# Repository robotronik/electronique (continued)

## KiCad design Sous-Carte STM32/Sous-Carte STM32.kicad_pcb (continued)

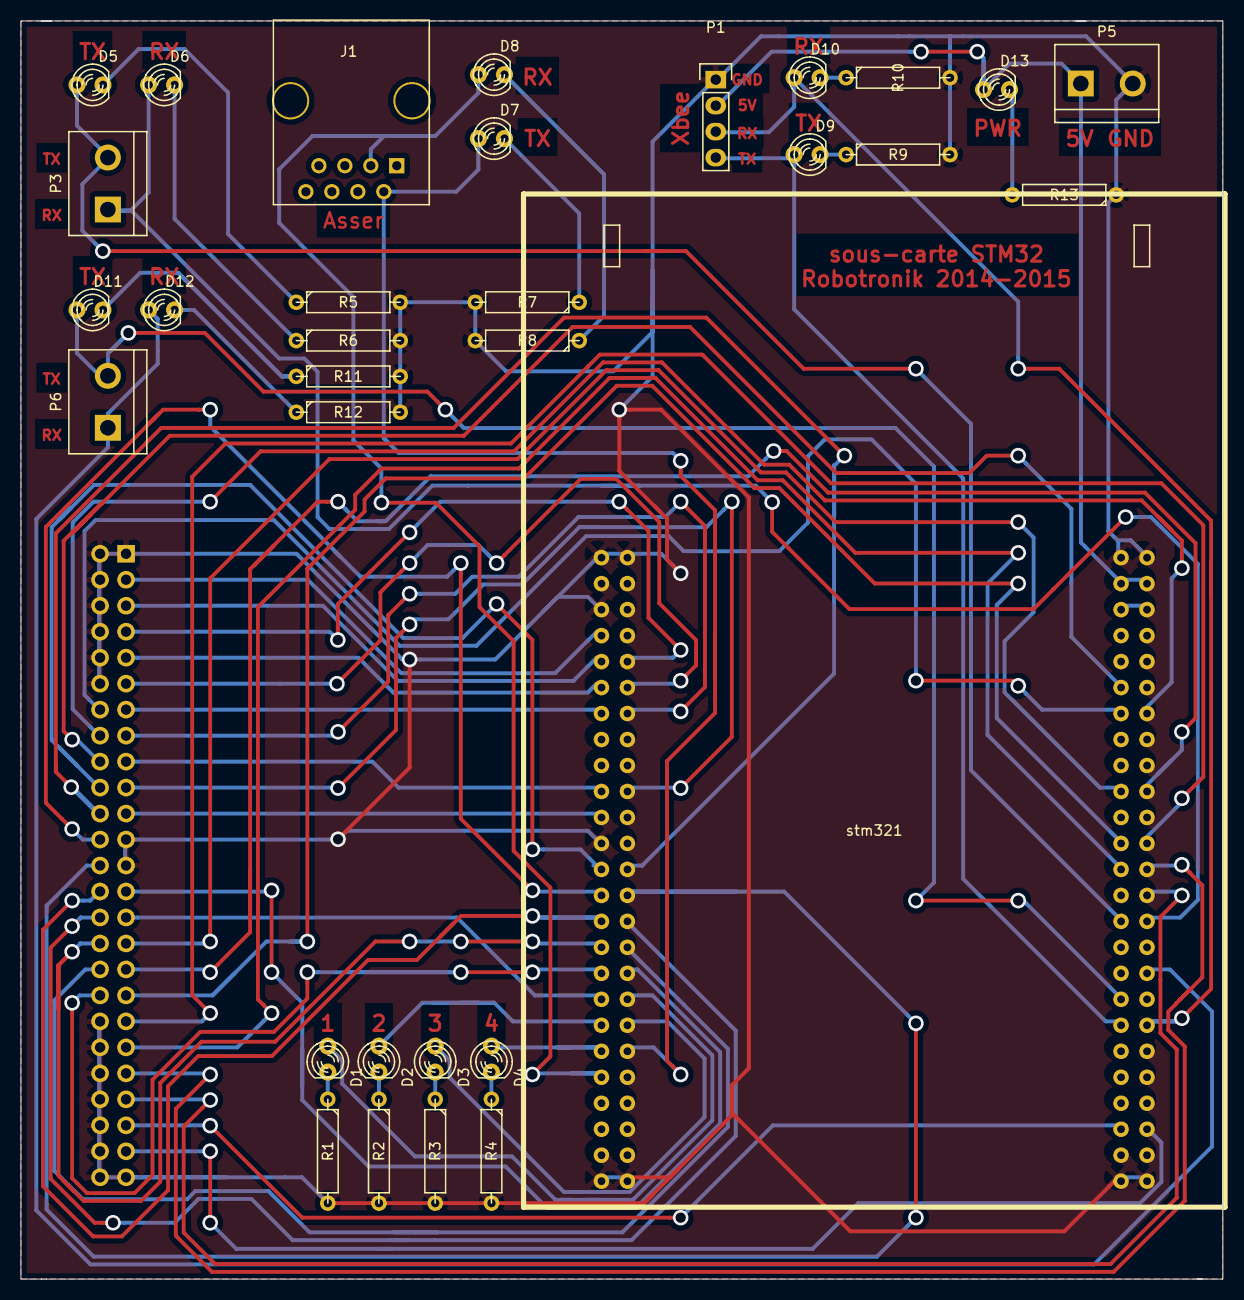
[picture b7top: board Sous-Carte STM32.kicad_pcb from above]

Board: 2 copper layers, 117.5 x 123.0 mm, 33 parts (1 on the bottom side), 61 nets.

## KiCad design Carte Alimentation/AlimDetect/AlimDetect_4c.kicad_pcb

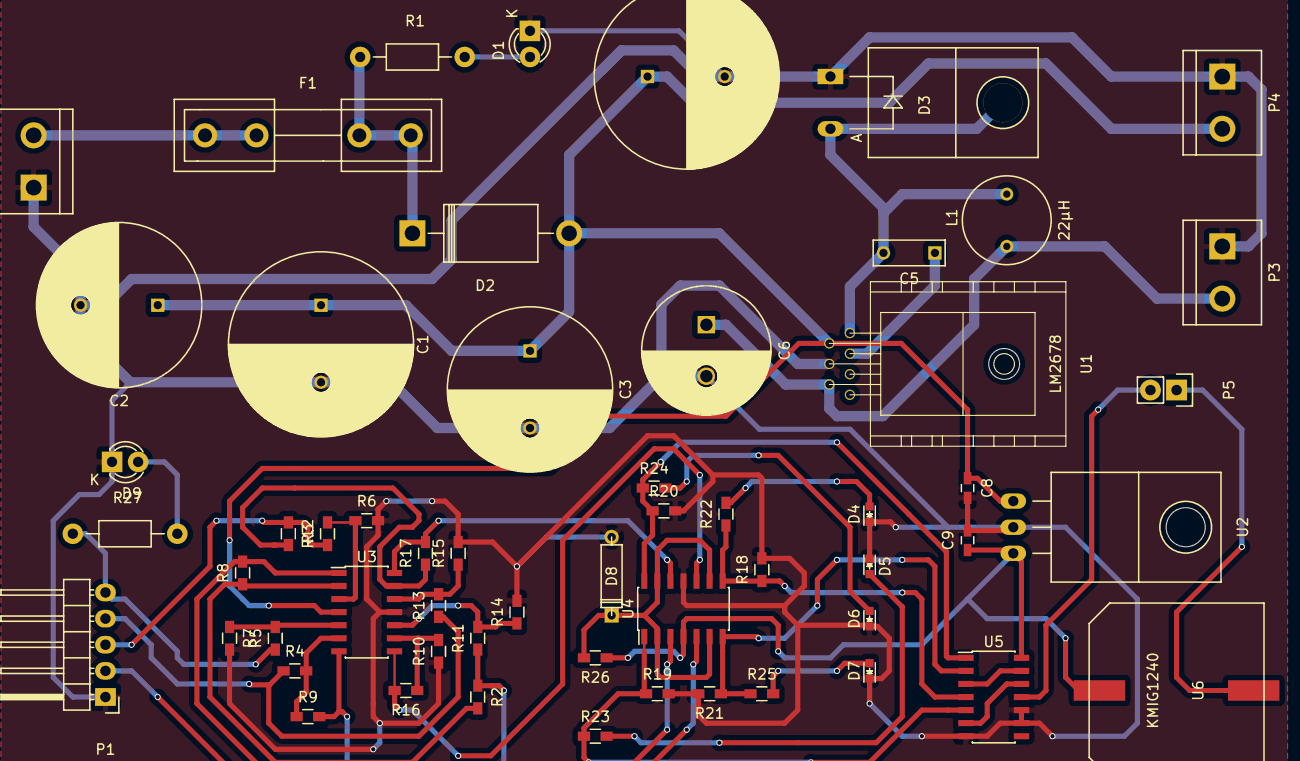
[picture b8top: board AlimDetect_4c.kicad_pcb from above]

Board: 2 copper layers, 57 parts (0 on the bottom side), 39 nets.

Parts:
C1: 820µF; C_Radial_D18_L36_P7.5
C2, C3: 680µF; C_Radial_D16_L25_P7.5
C5: 0.01µF; C_Rect_L7_W2.5_P5
C6: 820µF; C_Radial_D12.5_L25_P5
C8: 0.33µ; C_0603_HandSoldering
C9: 0.1µ; C_0603_HandSoldering
C10: 1200µF; C_Radial_D18_L36_P7.5
D1, D9: LED; LED-3MM
D2: 1N5404; Diode_DO-201AD_Horizontal_RM15
D3: DIODESCH; Diode_TO-220_Horizontal
D4, D5, D6, D7: LED; LED_0603
D8: 1N746A; D3
F1: F8AL250/SCHURTER 0031.8201; Fuseholder5x20_horiz_open_inline_Type-I
L1: 22µH; Coil_Trough_Hole
P1: CONN_01X05; Pin_Header_Angled_1x05
P2, P3, P4: CONN_01X02; bornier2
P5: CONN_01X02; Pin_Header_Straight_1x02
R1: 680; Resistor_Horizontal_RM10mm
R2, R3, R4, R5, R6, R7, R8, R9, R10, R11, R12, R13, R14, R15, R16, R17: R; R_0603_HandSoldering
R18, R19, R20, R21: 15k; R_0603_HandSoldering
R22, R23, R24, R25: 150; R_0603_HandSoldering
R26: 82; R_0603_HandSoldering
R27: 820; Resistor_Horizontal_RM10mm
U1: LM2678; to220-7-horiz_5772
U2: 7805; TO-220_Neutral123_Horizontal
U3, U4: TLC274; SOIC-14_3.9x8.7mm_Pitch1.27mm
U5: 74LS08; SOIC-14_3.9x8.7mm_Pitch1.27mm
U6: KMIG1240; kmig1240

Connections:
+5V: C9.1, R26.1, U2.3, U4.4, U5.14, U6.1
/PWR_redressé: C1.1, C2.1, C3.1, C8.1, C10.1, D2.2, P4.2, U1.2, U2.1, U3.4
/Vref: D8.1, R26.2, U4.2, U4.6, U4.9, U4.13
GND: C1.2, C2.2, C3.2, C6.2, C8.2, C9.2, C10.2, D1.1, D3.1, D4.1, D5.1, D6.1, D7.1, D8.2, D9.1, P1.1, P2.1, P3.1, P4.1, R6.2, R7.2, R10.1, R14.2, R15.2, R18.2, R19.2, R20.2, R21.2, U1.4, U2.2, U3.11, U4.11, U5.7, U5.9, U5.10
unnamed: C5.1, U1.3
unnamed: C5.2, D3.2, L1.1, U1.1
unnamed: C6.1, L1.2, P3.2, U1.6
unnamed: D1.2, R1.2
unnamed: D2.1, F1.2, R1.1
unnamed: D4.2, R22.2
unnamed: D5.2, R23.2
unnamed: D6.2, R24.2
unnamed: D7.2, R25.2
unnamed: D9.2, R27.2
unnamed: F1.1, P2.2
unnamed: P1.2, R2.1, R11.1
unnamed: P1.3, R3.1, R12.1
unnamed: P1.4, R4.1, R13.1
unnamed: P1.5, R5.1, R27.1
unnamed: P5.1, U6.2
unnamed: P5.2, U5.11
unnamed: R2.2, R8.1, U3.2
unnamed: R3.2, R6.1, U3.3
unnamed: R4.2, R9.1, U3.6
unnamed: R5.2, R7.1, U3.5
unnamed: R8.2, U3.1, U4.3
unnamed: R9.2, U3.7, U4.5
unnamed: R10.2, R16.1, U3.9
unnamed: R11.2, R14.1, U3.10
unnamed: R12.2, R17.1, U3.13
unnamed: R13.2, R15.1, U3.12
unnamed: R16.2, U3.8, U4.10
unnamed: R17.2, U3.14, U4.12
unnamed: R18.1, R22.1, U4.8, U5.4
unnamed: R19.1, R23.1, U4.1, U5.5
unnamed: R20.1, R24.1, U4.14, U5.1
unnamed: R21.1, R25.1, U4.7, U5.2
unnamed: U5.6, U5.12
unnamed: U5.3, U5.13

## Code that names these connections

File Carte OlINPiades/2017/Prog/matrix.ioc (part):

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Mcu.Name=STM32F303K(6-8)Tx
Mcu.Package=LQFP32
Mcu.UserName=STM32F303K8Tx
PA0.GPIOParameters=GPIO_Speed,GPIO_Label
PA0.GPIO_Label=PURGE
PA0.GPIO_Speed=GPIO_SPEED_FREQ_HIGH
PA0.Signal=GPIO_Output
PA1.GPIOParameters=GPIO_Speed,GPIO_Label
PA1.GPIO_Label=BLANK
PA1.GPIO_Speed=GPIO_SPEED_FREQ_HIGH
PA1.Signal=GPIO_Output
PA10.GPIOParameters=GPIO_Speed,GPIO_Label
PA10.GPIO_Label=SERIAL_IN
PA10.GPIO_Speed=GPIO_SPEED_FREQ_HIGH
PA10.Signal=GPIO_Output
PA11.GPIOParameters=GPIO_Speed,GPIO_Label
PA11.GPIO_Label=CLK_COL
PA11.GPIO_Speed=GPIO_SPEED_FREQ_HIGH
PA11.Signal=GPIO_Output
PA12.GPIOParameters=GPIO_Speed,GPIO_Label
PA12.GPIO_Label=LATCH_COL
PA12.GPIO_Speed=GPIO_SPEED_FREQ_HIGH
PA12.Signal=GPIO_Output
PA13.Mode=Serial_Wire
PA13.Signal=SYS_JTMS-SWDIO
PA14.Mode=Serial_Wire
PA14.Signal=SYS_JTCK-SWCLK
PA2.Mode=Asynchronous
PA2.Signal=USART2_TX
PA3.Mode=Asynchronous
PA3.Signal=USART2_RX
PA4.GPIOParameters=GPIO_Speed,GPIO_Label
PA4.GPIO_Label=DATA
PA4.GPIO_Speed=GPIO_SPEED_FREQ_HIGH
PA4.Signal=GPIO_Output
PA5.GPIOParameters=GPIO_Speed,GPIO_Label
PA5.GPIO_Label=LINE_4
PA5.GPIO_Speed=GPIO_SPEED_FREQ_HIGH
PA5.Signal=GPIO_Output
PA6.GPIOParameters=GPIO_Speed,GPIO_Label
PA6.GPIO_Label=LINE_3
PA6.GPIO_Speed=GPIO_SPEED_FREQ_HIGH
PA6.Signal=GPIO_Output
PA7.GPIOParameters=GPIO_Speed,GPIO_Label
PA7.GPIO_Label=LINE_2
PA7.GPIO_Speed=GPIO_SPEED_FREQ_HIGH
PA7.Signal=GPIO_Output
PB0.GPIOParameters=GPIO_Speed,GPIO_Label
PB0.GPIO_Label=LINE_1
PB0.GPIO_Speed=GPIO_SPEED_FREQ_HIGH
PB0.Signal=GPIO_Output
PB1.GPIOParameters=GPIO_Speed,GPIO_Label
PB1.GPIO_Label=LINE_0
PB1.GPIO_Speed=GPIO_SPEED_FREQ_HIGH
PB1.Signal=GPIO_Output
RCC.HSEPLLFreq_Value=8000000
RCC.HSE_VALUE=8000000
RCC.SYSCLKFreq_VALUE=64000000
RCC.SYSCLKSourceVirtual=RCC_SYSCLKSOURCE_PLLCLK
board=matrix

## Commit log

2015-01-08 added anciens
2015-01-08 added ancienne carte alim
2015-01-08 Created new project
2015-01-08 just some minor changes
2015-01-09 lots of modifs and added gitignore
2015-01-16 clean and gitignore
2015-01-16 added more in gitignore
2015-01-22 added some files
2015-02-05 créé pdf
2015-02-05 clean
2015-02-12 add datasheet
2015-02-27 add carte alim 2015, first revision
2015-03-14 déplacement dans un sous-dossier
2015-03-14 added chargeur plomb
2015-03-14 .gitignore is now working
2015-03-17 added alim2015Altium
2015-03-18 créé lib STM32, ajout projet alim-Altium
2015-03-18 added description and folder
2015-03-18 added carte olinpiades
2015-03-18 clean in chargeur plomb
2015-03-19 ajous carte actioneur
2015-03-19 mod altium
2015-03-22 carte alim v2
2015-03-22 oubli sauvegarde
2015-03-22 plan de masse
2015-03-22 proposition de sous carte pour le STM32
2015-03-22 début pcb
2015-03-23 some small modif and export
2015-03-27 moved electronic libraries
2015-03-27 fin schemas + début routage
2015-03-27 ajout led power
2015-03-27 correction connection masse
2015-03-27 correction connection masse 2
2015-03-27 correction connection uart3_rx
2015-03-27 correction connection uart5
2015-03-28 routage
2015-03-28 essayé d'avancer
2015-03-28 on avance
2015-03-29 début carte actionneurs capteurs
2015-03-29 clean and rename
2015-03-30 fin schéma carte actionneurs capteurs
2015-03-30 routage carte actionneurs capteurs (pas fini)
2015-04-01 routage fini mais à nettoyer
2015-04-01 fin routage
2015-04-01 correction norme bornier alim
2015-04-01 fini carte actionneurs-capteurs
2015-04-02 some clean carte alim + export
2015-04-02 re-export carte actionneurs capteurs
2015-04-02 routage sous carte stm 32
2015-04-02 correction ref pont en H
2015-04-03 plus que 3 piste a router 2 ou trois truc a revoir
2015-04-04 routage sous carte stm32 fini reste a agrandir la carte
2015-04-04 agrandissement de la carte + ajout fil de masse
2015-04-04 début changement diamètre via
2015-04-04 remplacement via
2015-04-05 remplacement presque terminé
2015-04-05 via totalement remplacés (à verifier) + DRC ok
2015-04-05 ajout texte et plan de masse
2015-04-05 nettoyage
2015-04-06 ajout texte
2015-04-06 DRC ok
2015-04-07 bougé la carte
2015-04-08 revert mirrored texts
2015-04-08 updated exported plots
2015-04-08 saved with settings
2015-04-08 saved with settings alim
2015-04-08 added exported plots for alim
2015-04-10 description de l'utilisation des pins du stm32
2015-04-27 mini carte actionneurs-capteurs
2015-05-04 ajout des pdfs corrects
2015-05-08 correction : remplacement d'une zener par une schottky
2015-05-08 ajout régul 5V qui avait disparu
2015-05-08 complete le commit précédent
2015-05-11 ajout commentaire pour remapper les capteur sur les pins ADC
2015-05-11 ajout commentaire pour remapper les capteurs sur les pins IO
2015-09-09 moved 2014 project to 2014 folder
2015-09-09 added 2015 carte olinpiades
2015-09-09 avancé plaque leds
2015-09-09 inversion sens leds
2015-09-09 inversion sens leds (oups)
2015-09-09 quelques modifs
2015-09-09 ajout rangée de leds manquante
2015-09-09 ajout jonctions
2015-09-09 all good
2015-09-09 erreurs corrigées
2015-09-09 reste alim puis pisa
2015-09-09 nouveaux composants plus petits
2015-09-09 added kicad pcb file
2015-09-09 propre
2015-09-09 normalement c'est fini à peu pros
2015-09-09 ajout pwr_flags
2015-09-09 some clean
2015-09-09 deleted cache lib
2015-09-09 changé composant
2015-09-09 ajouté pcb
2015-09-09 ajouté footprints comme il faut
2015-09-09 séparation composants
2015-09-09 placement des leds
2015-09-09 proposition placement composants
2015-09-10 retourne leds
2015-09-10 ajoute une face de piste de led
2015-09-10 ajoute l'autre face de piste de leds
2015-09-10 ajoute pistes coté demux
2015-09-10 ajoute piste du driver vers leds
2015-09-10 alim coté démux
2015-09-10 ajoute les pistes de signals
2015-09-10 ajoute la partie pour flasher le pic
2015-09-10 manque partie alim
2015-09-10 ajoute capa de découplage
2015-09-10 ajoute capa de découplage 2 ?
2015-09-10 ajoute composant 74HC4514D à la lib
2015-09-11 remplacement du démux
2015-09-11 ajoute pistes capa tantale
2015-09-11 divisé la carte en 2
2015-09-11 ajout pinheader
2015-09-11 euh…
2015-09-11 ajoute pin header sur le shémas et supprime les leds sur le pcb
2015-09-11 place les barrettes de 16 pins sur le PCB
2015-09-11 avancé matrice
2015-09-11 retourne le pin header
2015-09-11 cable le driver
2015-09-11 fini plaque de leds
2015-09-11 ajoute les pistes coté démux
2015-09-11 cablage PIC vers démux et driver
2015-09-11 cablage autre éléments du PIC
2015-09-11 enleve les anciennes pistes
2015-09-11 enleve condensateur inutile
2015-09-11 meilleur agencement
2015-09-11 meilleur agencement coté driver
2015-09-11 déplace les broche d'uart de de programmation
2015-09-11 resserre les switchs
2015-09-11 déplace connecteurs UART
2015-09-11 retourné matrice, exporté pdfs
2015-09-11 change la face des pins receptrice de la matrice de leds
2015-09-11 déplace les composant d'alim dans leur zone
2015-09-11 connection logique avec regul ok
2015-09-11 cablage alim
2015-09-11 DRC ok sauf pour connecteur d'UART ?
2015-09-12 change coté des pistes des broches de la matrice de leds
2015-09-15 rapproche le démux des pins headers
2015-09-15 rapproche le dsPIC
2015-09-15 nettoyage de pistes
2015-09-15 nettoyage et changement de taille de certaines pistes
2015-09-15 ajout plan de masse et nom de carte
2015-09-16 plus propre
2015-10-16 bougé les librairies
2016-01-07 Circuit de détection du niveau des batteries
2016-01-07 Rangement dossier des cartes alim'
2016-01-07 Condensateurs de découplage sur AlimDetect_4c.sch
2016-01-07 Ajout librairie composant+footprint kmig1240 (buzzer)
2016-01-07 Création composant LM2678.lib (regul step-down)
2016-01-07 Regul 5V à la bonne place
2016-01-07 Annotation de AlimDetect_4c.sch
2016-01-07 Supression de fichiers déplacés dans Carte Alimentation/Alim_2015
2016-01-07 Correction logique de détection du niveau des batteries
2016-01-07 Ajout de la logique de détection de la batterie elec (2 cellules)
2016-01-08 ERC ok pour 2 et 4 celulles
2016-01-12 Librairie de footprint TO-220, en particulier celle du LM2678 (to220-7-horiz_5772)
2016-01-14 Ajout de la librairie buzz (buzzer)
2016-01-18 réparation carte actionneurs-capteurs
2016-01-18 réparation carte actionneurs capteurs mini
2016-01-18 renames
2016-01-18 renamed and repaired carte alim 2015 ; still need 7905
2016-01-18 réparé alimDetect 2C
2016-01-21 Réparation de 4c.sch et 2c.sch
2016-01-21 Correction logique de détection
2016-01-27 Réparation Alim 2015, remplacement du 7905 (régul -) par 7805 (régul +)
2016-01-27 Réparation Carte Olinpiades Logique + Matrice
2016-01-27 Réparation Sous-Carte STM32
2016-01-30 Valeurs des composants critiques
2016-01-30 Procédure de design du LM2678, footprint de l'inductance
2016-01-30 Netlist et association des modules pour 4c
2016-01-30 Routage carte 4c
2016-01-30 Ajout cavalier buzzer et plans de masse 4c
2016-02-12 réparation sous carte, schéma
2016-02-12 ajout stm32 aux libs
2016-02-12 réparation sous carte stm32, pcb, ok !
2016-02-12 stupid clean of path to lib
2016-02-12 amélioré empreinte stm32
2016-02-12 fix sous carte stm32
2016-03-21 Ajustement avant réalisation des PCB par Pisa
2016-03-21 Création du shield 12V -> 7.5V
2016-03-21 Typhons PDF des cartes Alim
2016-03-21 Ajout d'une librairie de potentiomètres
2016-03-21 Filtre RC ajustable pour filtrer le signal des caméras Freescale
2016-04-05 ajout sous carte asser stm32
2016-04-06 ajout pas mal de trucs + pcb
2016-04-06 ok see it
2016-04-06 Finalisation RC Freescale
2016-04-06 Ajout composant & empreinte du régul DC/DC dsn2596
2016-04-06 Schéma et routage de la carte alim basée sur les réguls DC/DC
2016-04-06 changé de timer un codeur
2016-04-06 AJout condo céramiques aux sorties régulées (LiPo_module)
2016-04-06 Condo céramiques LiPo_module sur le sch
2016-04-06 Connection driver moteurs Ss-carte asser 2A, ajout des pinoches
2016-04-06 Modification connexion codeurs <-> timers
2016-04-06 Valeurs résistances ss-carte asser 2A
2016-04-07 Sous carte asser dite -- arraignée - avec pinoche et tout, routée
2016-04-07 schematic seems ok, ongoing routing
2016-04-07 move before merge
2016-04-07 some cleaning
2016-04-08 Ajout pin_header Uart Asser
2016-04-08 Tracé PDF de la sous carte Asser 2A et de la carte alim
2016-04-08 asser 1A : routé
2016-04-08 asser 1A : corrections sur le routage + trous visses
2016-04-08 asser 1A : removed serial tx protection resistor, leaves some space for the screw's head
2016-04-09 added B-plugs for power
2016-04-09 added a nice logo :)
2016-04-10 asser 1A : BOM + ready for pisa !
2016-04-10 silly mistake when plotting
2016-04-13 Schéma de la carte stratégie F429i
2016-04-13 asser 1A : corrected zif sockets
2016-04-14 Ajout conf coquillages
2016-04-14 Footprint stm32f4i-disco
2016-04-21 asser 1A : inversed serial tx and rx labels, damn
2016-04-28 Coorection empreinte F429i
2016-04-28 Ajout pin couleur d'équipe
2016-04-28 fix empreinte stm32
2016-04-28 changement footprint stm32 sur le pcb
2016-04-28 ajout connecteur couleur
2016-04-29 Redimensionnement carte
2017-09-15 Création carte OlINP 2017
2017-09-16 Ajout composant sch STM32F303K8
2017-09-16 Suppression anciens fichiers
2017-09-16 Schéma yeux OlINP 2017
2017-09-18 Ajout composants OlINP divers (demux, NOT)
2017-09-18 Ajout empreintes Molex
2017-09-18 Abandon des yeux pannélisés
2017-09-18 Schéma et association d'empreintes des yeux OlINP (matrice et logique)
2017-09-19 Librairie de logos Silkscreen
2017-09-19 Ajout des regul sch avec les bonnes pins (saloperie de noms)
2017-09-19 Schéma carte Logique fini
2017-09-19 Association d'empreintes carte Logique
2017-09-19 Routage carte Logique fini, à vérifier
2017-09-19 Ajout des librairies au projet de la carte Logique
2017-09-20 Correction du sens des connecteurs
2017-09-23 Empreinte résistance de puissance CMS
2017-09-23 Composants sch Ol'INP 2017
2017-09-23 Nouveau driver Ol'INP à base de PNP's
2017-09-23 Routage nouveau driver Ol'INP
2017-09-23 Routage pour de vrai du nouveau driver Ol'INP
2017-09-23 Matrice Ol'INP 32*32 sch + routage
2017-09-23 Empreinte du gros logo robotronik
2017-09-23 Ajout régul 3.3 overkill
2017-09-23 Passage de toute la carte en 3.3V
2017-09-23 Finalisation matrice
2017-10-01 début prog
2017-10-01 sélection des lignes et purge
2017-10-01 matrice maitre
2017-10-02 huart config
2017-10-05 fake projet
2017-10-05 works
2017-10-05 readme
2017-10-05 Makefile modif
2017-10-05 UART
2017-10-06 Modifications avant 1er envoi
2017-10-06 Ficheirs Gerber
2017-10-06 rename
2017-10-06 final matrix
2017-10-06 new makefile
2017-12-17 modif empreinte STM32
2017-12-26 modif marquage
2018-01-05 ajout 3.3V pour esp
2018-01-05 gerber
